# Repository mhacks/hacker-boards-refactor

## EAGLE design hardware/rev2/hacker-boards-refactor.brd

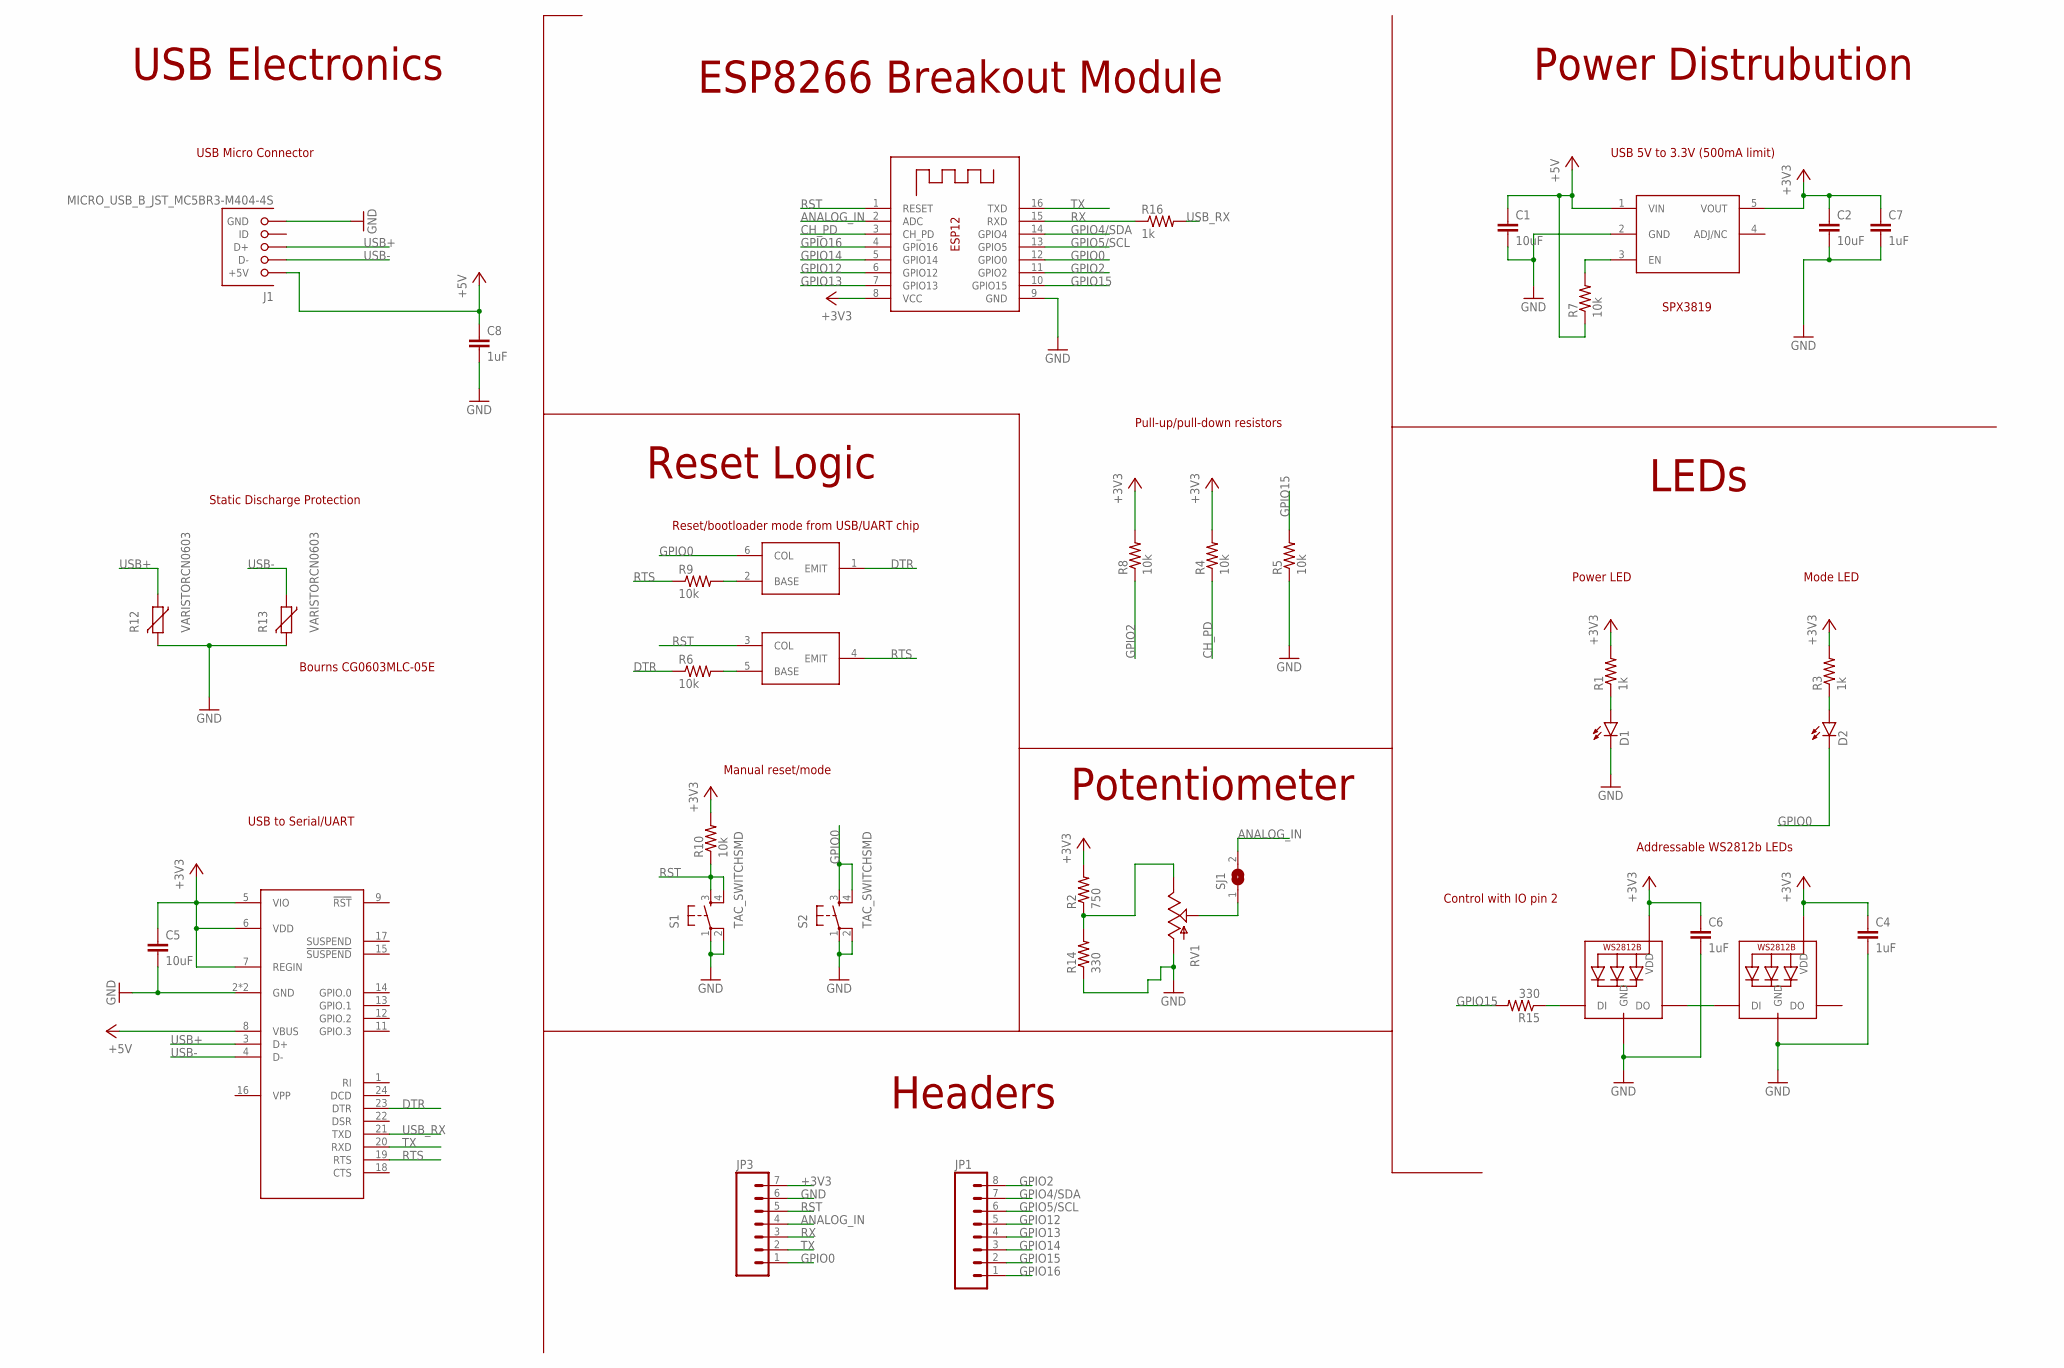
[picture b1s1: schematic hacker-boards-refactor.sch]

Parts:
C1, C2, C5: 10uF; C0805
C4, C6, C7, C8: 1uF; C0402
D1, D2: LED0603; LED-0603
J1: MICRO_USB_B_JST_MC5BR3-M404-4S; USB_MICRO_B-JST-MC5BR3-M404-4S-TB
JP1: M08; 1X08_ROUND
JP3: M07; 1X07
LED1, LED2: WS2812B5050; WS2812B
R1, R3, R16: 1k; R0402
R2: 750; R0402
R4, R5, R6, R7, R8, R9, R10: 10k; R0402
R12, R13: VARISTORCN0603; CT/CN0603
R14, R15: 330; R0402
RV1: POTALPS-KIT; ALPS_POT_KIT
S1, S2: TAC_SWITCHSMD; TACTILE-SWITCH-SMD
SJ1: SJ
U$2: AP2112; SOT23-5L
U$3: CP2104; QFN24_4X4
U$4: MBT3904DW1T1G; SOT363
X1: ESP-12

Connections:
+3V3: C2.1, C4.1, C5.1, C6.1, C7.1, JP3.7, LED1.1-VDD (VDD), LED2.1-VDD (VDD), R1.2, R2.2, R3.2, R4.2, R8.2, R10.2, U$2.5 (VOUT), U$3.5 (VIO), U$3.6 (VDD), U$3.7 (REGIN), X1.8 (VCC)
+5V: C1.1, C8.1, J1.1 (+5V), R7.1, U$2.1 (VIN), U$3.8 (VBUS)
ANALOG_IN: JP3.4, SJ1.2, X1.2 (ADC)
CH_PD: R4.1, X1.3 (CH_PD)
DTR: R6.1, U$3.23 (DTR), U$4.1 (EMIT)
GND: C1.2, C2.2, C4.2, C5.2, C6.2, C7.2, C8.2, D1.C, J1.5 (GND), JP3.6, LED1.3-GND (GND), LED2.3-GND (GND), R5.1, R12.2, R13.2, R14.1, RV1.P$3 (A), S1.1, S1.2, S2.1, S2.2, U$2.2 (GND), U$3.2 (GND), U$3.25 (GND), X1.9 (GND)
GPIO0: D2.C, JP3.1, S2.3, S2.4, U$4.6 (COL), X1.12 (GPIO0)
GPIO2: JP1.8, R8.1, X1.11 (GPIO2)
GPIO4/SDA: JP1.7, X1.14 (GPIO4)
GPIO5/SCL: JP1.6, X1.13 (GPIO5)
GPIO12: JP1.5, X1.6 (GPIO12)
GPIO13: JP1.4, X1.7 (GPIO13)
GPIO14: JP1.3, X1.5 (GPIO14)
GPIO15: JP1.2, R5.2, R15.2, X1.10 (GPIO15)
GPIO16: JP1.1, X1.4 (GPIO16)
unnamed: D1.A, R1.1
unnamed: D2.A, R3.1
unnamed: R2.1, R14.2, RV1.P$1 (E)
unnamed: LED1.2-DOUT (DO), LED2.4-DIN (DI)
unnamed: LED1.4-DIN (DI), R15.1
unnamed: R7.2, U$2.3 (EN)
unnamed: R9.2, U$4.2 (BASE)
unnamed: R6.2, U$4.5 (BASE)
unnamed: RV1.P$2 (S), SJ1.1
RST: JP3.5, R10.1, S1.3, S1.4, U$4.3 (COL), X1.1 (RESET)
RTS: R9.1, U$3.19 (RTS), U$4.4 (EMIT)
RX: JP3.3, R16.1, X1.15 (RXD)
TX: JP3.2, U$3.20 (RXD), X1.16 (TXD)
USB+: J1.3 (D+), R12.1, U$3.3 (D+)
USB-: J1.2 (D-), R13.1, U$3.4 (D-)
USB_RX: R16.2, U$3.21 (TXD)

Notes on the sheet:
Power Distrubution
LEDs
Headers
Potentiometer
Reset Logic
ESP8266 Breakout Module
USB Electronics
USB Micro Connector
Static Discharge Protection
USB to Serial/UART
Pull-up/pull-down resistors
Reset/bootloader mode from USB/UART chip
Manual reset/mode
Power LED
Mode LED
Addressable WS2812b LEDs
Control with IO pin 2
USB 5V to 3.3V (500mA limit)
Bourns CG0603MLC-05E
SPX3819

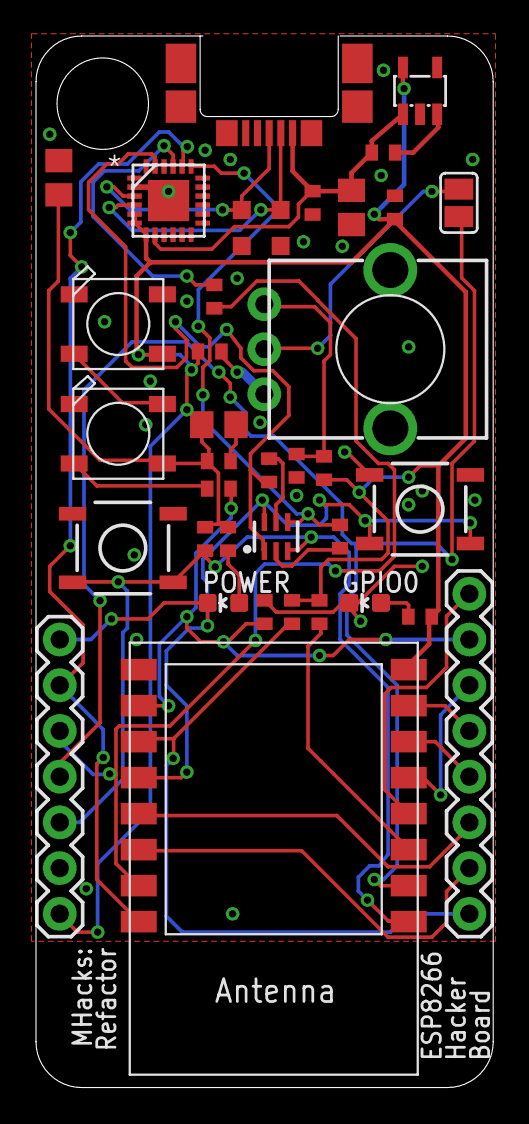
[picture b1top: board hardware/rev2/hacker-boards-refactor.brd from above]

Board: 2 copper layers, 25.4 x 58.4 mm, 38 parts (1 on the bottom side), 31 nets.

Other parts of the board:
U$5: EDGY-LOGO-8BIT

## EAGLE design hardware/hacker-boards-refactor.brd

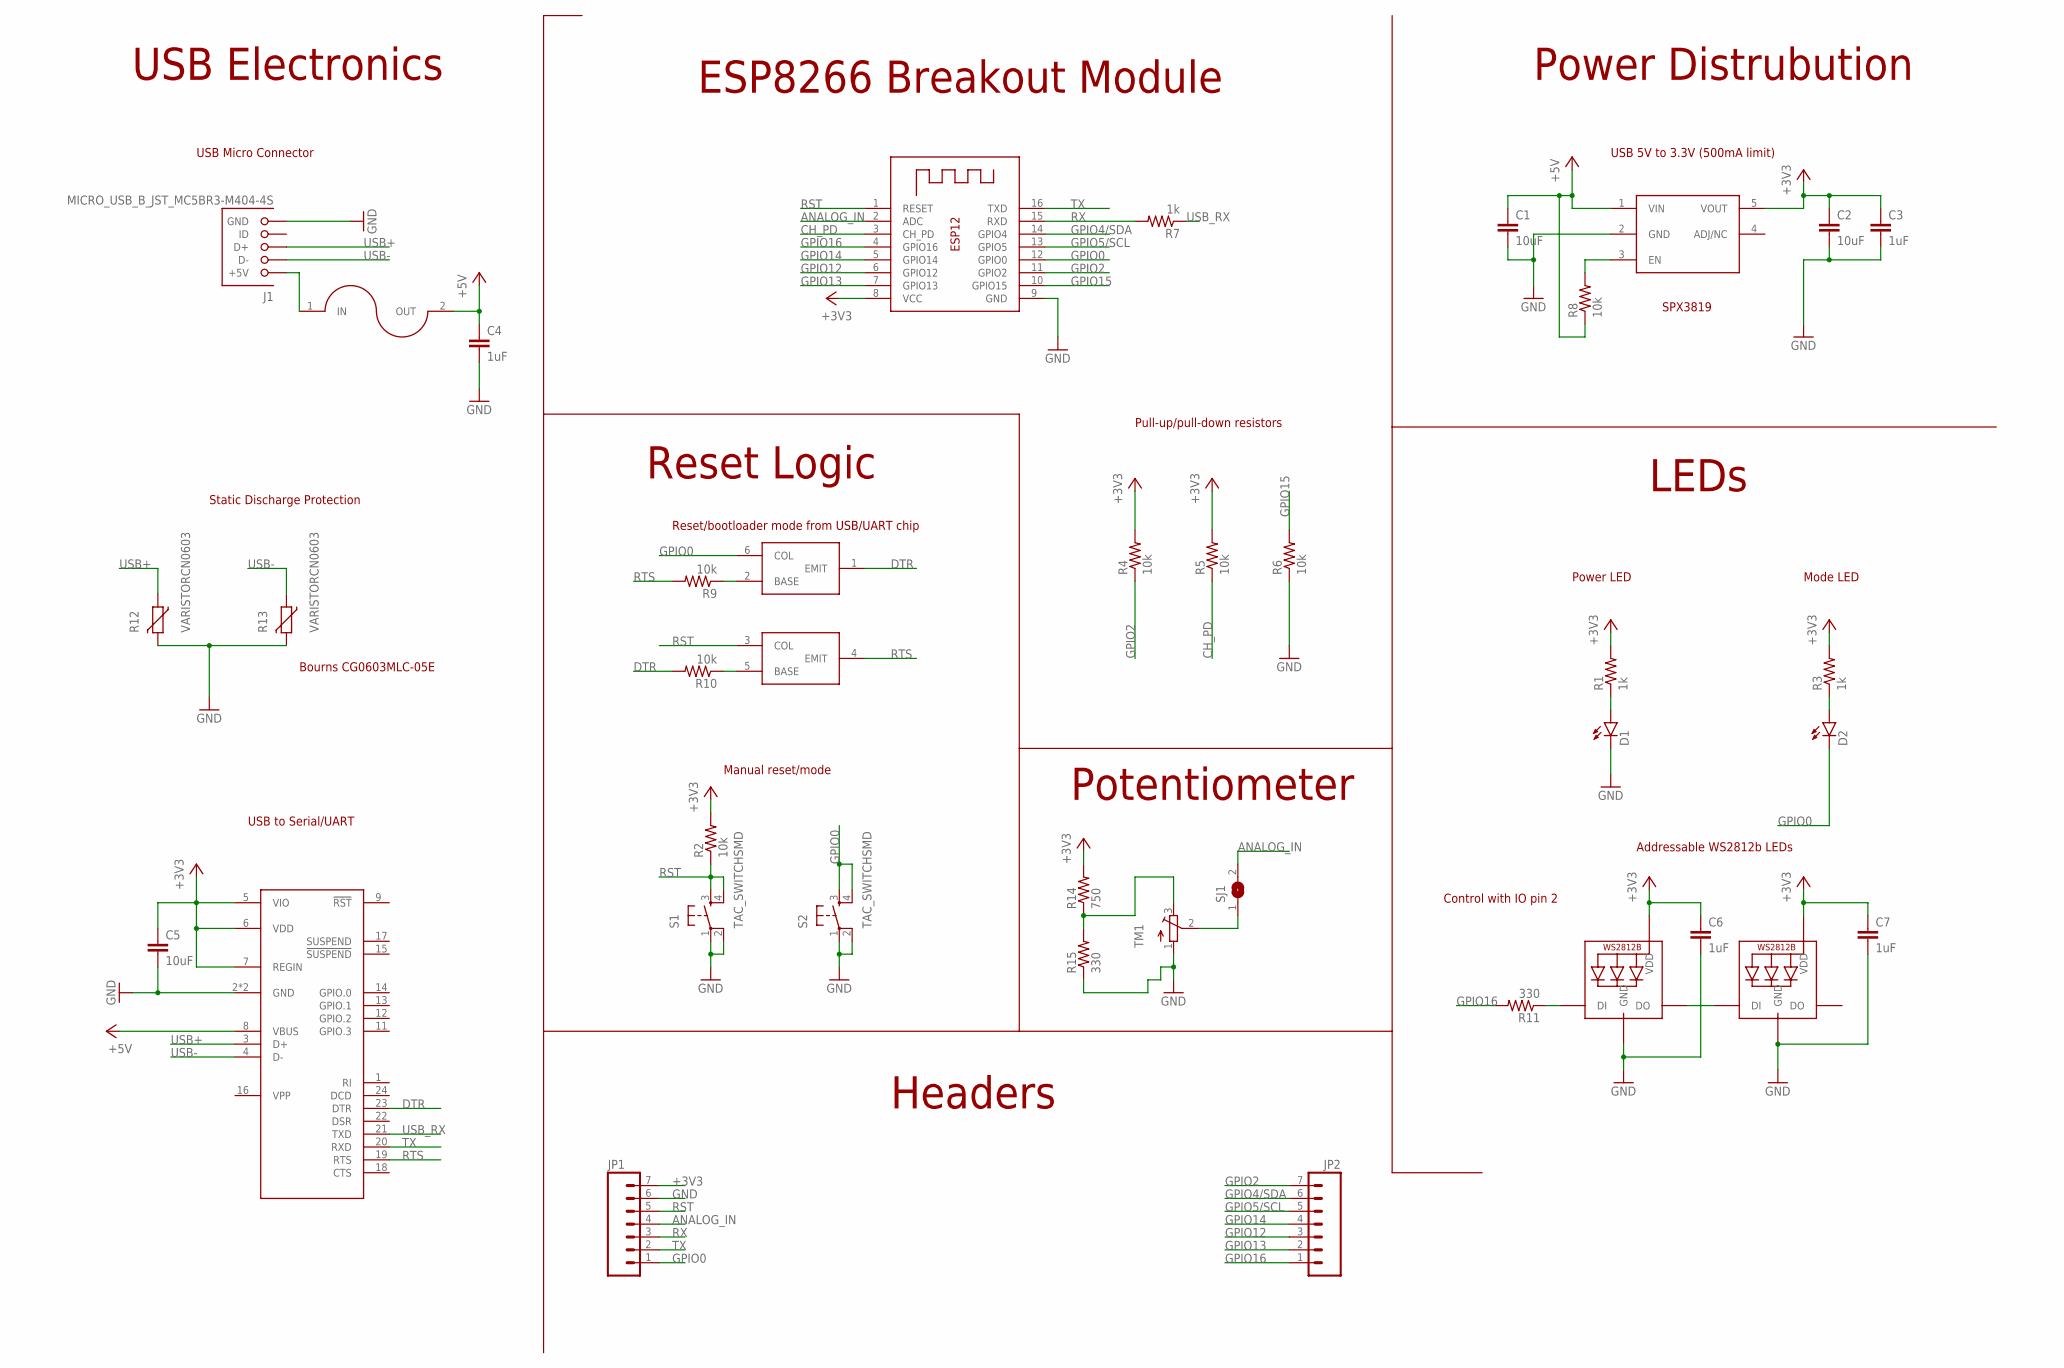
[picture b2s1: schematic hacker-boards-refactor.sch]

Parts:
C1, C2, C5: 10uF; C0805
C3, C4, C6, C7: 1uF; C0805
D1, D2: LED0603; LED-0603
J1: MICRO_USB_B_JST_MC5BR3-M404-4S; USB_MICRO_B-JST-MC5BR3-M404-4S-TB
JP1, JP2: M07LONGPADS; 1X07_LONGPADS
LED1, LED2: WS2812B5050; WS2812B
R1, R3, R7: 1k; R0805
R2, R4, R5, R6, R8, R9, R10: 10k; R0805
R11, R15: 330; R0805
R12, R13: VARISTORCN0603; CT/CN0603
R14: 750; R0805
S1, S2: TAC_SWITCHSMD; TACTILE-SWITCH-SMD
SJ1: SJ
TM1: TRIMPOTTC33X; TC33X
U$1: USB-FUSE; L1812
U$2: AP2112; SOT23-5L
U$3: CP2104; QFN24_4X4
U$4: MBT3904DW1T1G; SOT363
X1: ESP-12

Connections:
+3V3: C2.1, C3.1, C5.1, C6.1, C7.1, JP1.7, LED1.1-VDD (VDD), LED2.1-VDD (VDD), R1.2, R2.2, R3.2, R4.2, R5.2, R14.2, U$2.5 (VOUT), U$3.5 (VIO), U$3.6 (VDD), U$3.7 (REGIN), X1.8 (VCC)
+5V: C1.1, C4.1, R8.1, U$1.2 (OUT), U$2.1 (VIN), U$3.8 (VBUS)
ANALOG_IN: JP1.4, SJ1.2, X1.2 (ADC)
CH_PD: R5.1, X1.3 (CH_PD)
DTR: R10.2, U$3.23 (DTR), U$4.1 (EMIT)
GND: C1.2, C2.2, C3.2, C4.2, C5.2, C6.2, C7.2, D1.C, J1.5 (GND), JP1.6, LED1.3-GND (GND), LED2.3-GND (GND), R6.1, R12.2, R13.2, R15.1, S1.1, S1.2, S2.1, S2.2, TM1.1 (A), U$2.2 (GND), U$3.2 (GND), U$3.25 (GND), X1.9 (GND)
GPIO0: D2.C, JP1.1, S2.3, S2.4, U$4.6 (COL), X1.12 (GPIO0)
GPIO2: JP2.7, R4.1, X1.11 (GPIO2)
GPIO4/SDA: JP2.6, X1.14 (GPIO4)
GPIO5/SCL: JP2.5, X1.13 (GPIO5)
GPIO12: JP2.3, X1.6 (GPIO12)
GPIO13: JP2.2, X1.7 (GPIO13)
GPIO14: JP2.4, X1.5 (GPIO14)
GPIO15: R6.2, X1.10 (GPIO15)
GPIO16: JP2.1, R11.2, X1.4 (GPIO16)
unnamed: D1.A, R1.1
unnamed: J1.1 (+5V), U$1.1 (IN)
unnamed: D2.A, R3.1
unnamed: R14.1, R15.2, TM1.3 (E)
unnamed: LED1.2-DOUT (DO), LED2.4-DIN (DI)
unnamed: LED1.4-DIN (DI), R11.1
unnamed: R8.2, U$2.3 (EN)
unnamed: R9.1, U$4.2 (BASE)
unnamed: R10.1, U$4.5 (BASE)
unnamed: SJ1.1, TM1.2 (S)
RST: JP1.5, R2.1, S1.3, S1.4, U$4.3 (COL), X1.1 (RESET)
RTS: R9.2, U$3.19 (RTS), U$4.4 (EMIT)
RX: JP1.3, R7.2, X1.15 (RXD)
TX: JP1.2, U$3.20 (RXD), X1.16 (TXD)
USB+: J1.3 (D+), R12.1, U$3.3 (D+)
USB-: J1.2 (D-), R13.1, U$3.4 (D-)
USB_RX: R7.1, U$3.21 (TXD)

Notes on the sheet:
Power Distrubution
LEDs
Headers
Potentiometer
Reset Logic
ESP8266 Breakout Module
USB Electronics
USB Micro Connector
Static Discharge Protection
USB to Serial/UART
Pull-up/pull-down resistors
Reset/bootloader mode from USB/UART chip
Manual reset/mode
Power LED
Mode LED
Addressable WS2812b LEDs
Control with IO pin 2
USB 5V to 3.3V (500mA limit)
Bourns CG0603MLC-05E
SPX3819

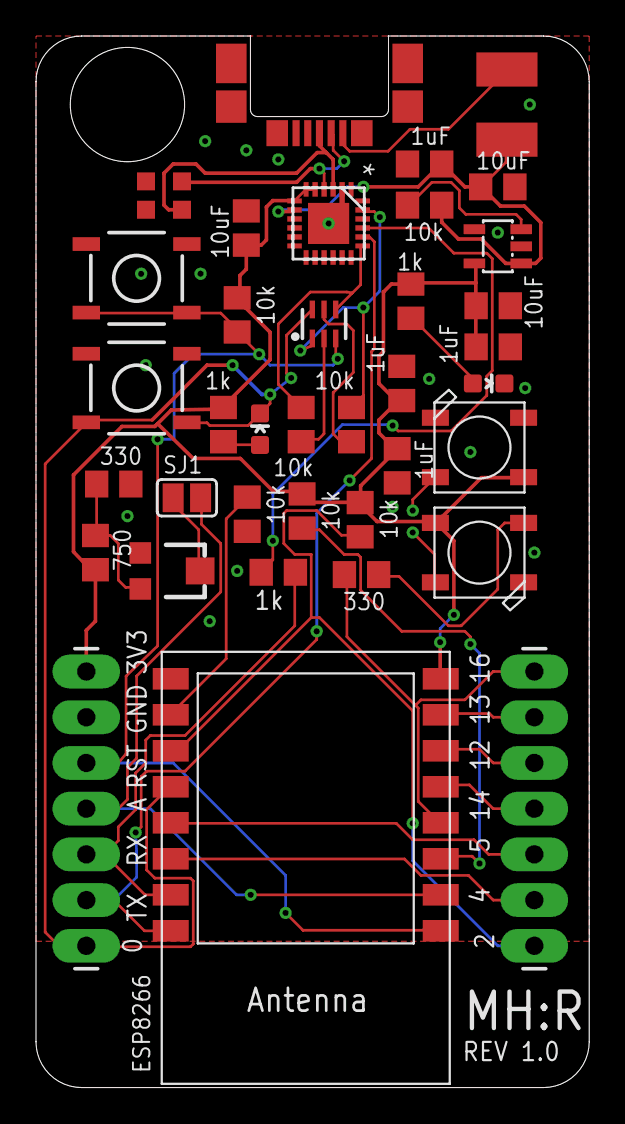
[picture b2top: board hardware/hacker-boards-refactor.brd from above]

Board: 2 copper layers, 30.7 x 58.4 mm, 38 parts (0 on the bottom side), 32 nets.

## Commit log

2015-12-19 Added README
2015-12-19 Added folder structure with library
2015-12-19 Updated .gitignore with github/github's Eagle recommendation, added Adafruit's ESP-12 module to the parts library
2015-12-19 Added a whole raft of other useful parts
2015-12-19 Initial Schematic Commit
2015-12-19 Added CP2104 to library
2015-12-19 Added 0402, 0603, 0805 resistors
2015-12-20 Added dual NPN transistor
2015-12-20 Added USB parts, reset logic, headers, LEDs. Cleaned up.
2015-12-20 Current limiting resistor on data pin of WS2812, decoupling caps on power lines
2015-12-20 Added potentiometer and ESD protection for USB
2015-12-20 Updated size of QFN24 package's thermal pad - was violating Osh Park's DRC
2015-12-20 Fixed pad sizes on the QFN24 part again - corners were breaking Osh Park's DRC
2015-12-21 Initial board commit (with autorouted traces), schematic cleanup
2015-12-21 Added header labels, fixed silk, cleared space for extra ESP-12 pads
2015-12-21 Slightly enlarged board for new headers, extensively tweaked silkscreen
2016-01-06 Preparing for second revision development
2016-01-06 Switched all capacitors and resistors besides 10uF to 0402 for smaller production size
2016-01-06 Shrank the board and re-placed components, looking for an optimized second prototyping run
2016-01-07 Added 5V/3V3 traces
2016-01-07 Removed fuse, played around/shrunk board dimensions some more
2016-01-08 First pass at routing
2016-01-08 Added polygons/planes to board
2016-01-11 Added huge solder stop area in the MHacks Refactor logo form
2016-01-11 Fixed D16 silkscreen
2016-01-11 Tweaked traces to make polygons better
2016-01-11 More polygon optimization
2016-01-28 Updated artwork
2016-02-17 Added first demo program
2016-02-19 Basic networking example with HTTP requests to mhacks.github.io that update the WS2812 LEDs
2016-02-19 Added more examples
2016-09-01 Rev4, cleaning up a bit
2016-09-07 Updated logo, small fixes on artwork
2016-09-08 Tiny routing changes to make DRC happy
2020-09-08 quick serial output fix
2020-09-08 Update netowrking demo for new wiFi Network
2020-09-08 Added library file for new logo

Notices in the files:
parts and their libraries:
SparkFun-Connectors: Licensing: Creative Commons ShareAlike 4.0 International - https://creativecommons.org/licenses/by-sa/4.0
